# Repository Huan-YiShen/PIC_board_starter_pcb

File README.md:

# PIC_board_starter_pcb
this is a tutorial from Waterloo Rocketry to demonstrate the PIC board and the KiCad workflow

## Process include
1. create custom symbol for PIC12(L)F1501
2. create Schematic
3. create PCB layout  
4. Generate Gerber and Drill File

## Schematic

## PCB layout

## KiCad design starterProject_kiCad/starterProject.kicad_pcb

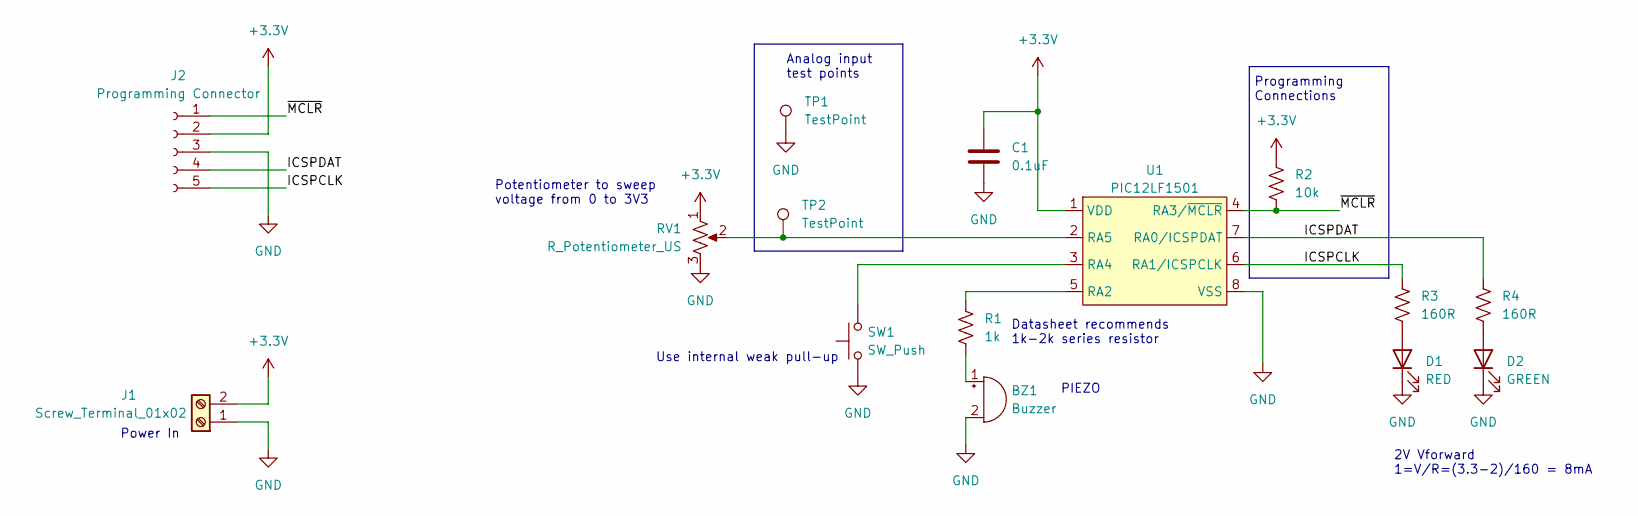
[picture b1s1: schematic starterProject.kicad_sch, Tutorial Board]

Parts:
BZ1: Buzzer; Buzzer_TDK_PS1240P02BT_D12.2mm_H6.5mm
C1: 0.1uF; C_0805_2012Metric_Pad1.18x1.45mm_HandSolder
D1: RED; LED_1206_3216Metric_Pad1.42x1.75mm_HandSolder
D2: GREEN; LED_1206_3216Metric_Pad1.42x1.75mm_HandSolder
J1: Screw_Terminal_01x02; TerminalBlock_Phoenix_PT-1,5-2-5.0-H_1x02_P5.00mm_Horizontal
J2: Programming Connector; PinHeader_5x2.54_SMD_90deg_952-3198-1-ND
R1: 1k; R_0805_2012Metric_Pad1.20x1.40mm_HandSolder
R2: 10k; R_0805_2012Metric_Pad1.20x1.40mm_HandSolder
R3, R4: 160R; R_0805_2012Metric_Pad1.20x1.40mm_HandSolder
RV1: R_Potentiometer_US; Potentiometer_Bourns_PTV09A-1_Single_Vertical
SW1: SW_Push; SW_PUSH_6mm
TP1, TP2: TestPoint; TestPoint_THTPad_2.0x2.0mm_Drill1.0mm
U1: PIC12LF1501; SOIC-8_3.9x4.9mm_P1.27mm

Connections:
+3.3V: C1.1, J1.2, J2.2, R2.1, RV1.1, U1.1 (VDD)
/ICSPCLK: J2.5, R3.1, U1.6 (RA1/ICSPCLK)
/ICSPDAT: J2.4, R4.1, U1.7 (RA0/ICSPDAT)
/~MCLR: J2.1, R2.2, U1.4 (RA3/~MCLR)
GND: BZ1.2 (+), C1.2, D1.1 (K), D2.1 (K), J1.1, J2.3, RV1.3, SW1.1, TP1.1, U1.8 (VSS)
unnamed: BZ1.1 (-), R1.2
unnamed: D1.2 (A), R3.2
unnamed: D2.2 (A), R4.2
unnamed: R1.1, U1.5 (RA2)
unnamed: RV1.2, TP2.1, U1.2 (RA5)
unnamed: SW1.2, U1.3 (RA4)

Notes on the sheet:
Use internal weak pull-up
2V Vforward 1=V/R=(3.3-2)/160 = 8mA
PIEZO
Analog input test points
Datasheet recommends 1k-2k series resistor
Potentiometer to sweep voltage from 0 to 3V3
Programming Connections
Power In

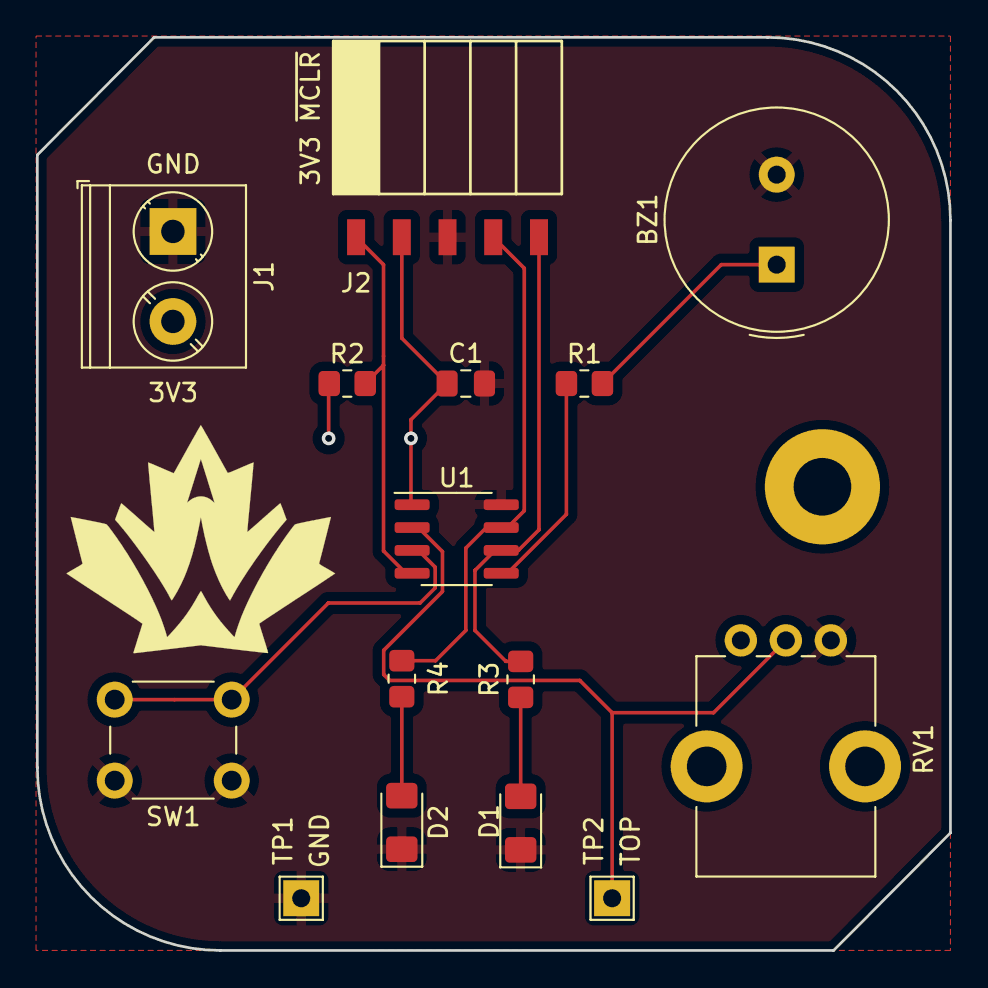
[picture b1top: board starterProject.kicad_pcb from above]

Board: 2 copper layers, 50.7 x 50.7 mm, 15 parts (0 on the bottom side), 11 nets.

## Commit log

2023-02-04 completed PCB layout
2023-02-15 added decore silkscreen and gerber
